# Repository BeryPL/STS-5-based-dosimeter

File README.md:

This is a terrible PCB design with LTSpice simulations for a STS-5 lamp based dosimeter circuit. This abomination is based on an old dosimeter design found on the internet, and was adopted to parts i had lying arround. Hence those weird resistor values and such. It does work tho. The goal is to create a fully working dosimeter circuit with a microcontroller for counting and sending information via BLE. 

Jest to okropny projekt PCB z symulacjami LTSpice dla obwodu dozymetru opartego na lampie STS-5. Ta abominacja jest oparta na starym projekcie dozymetru znalezionym w Internecie i została dostosowana do części, które miałem w pobliżu. Stąd te dziwne wartości rezystorów itp. Ale działa. Celem jest stworzenie w pełni działającego obwodu dozymetru z mikrokontrolerem do zliczania i wysyłania informacji przez BLE.

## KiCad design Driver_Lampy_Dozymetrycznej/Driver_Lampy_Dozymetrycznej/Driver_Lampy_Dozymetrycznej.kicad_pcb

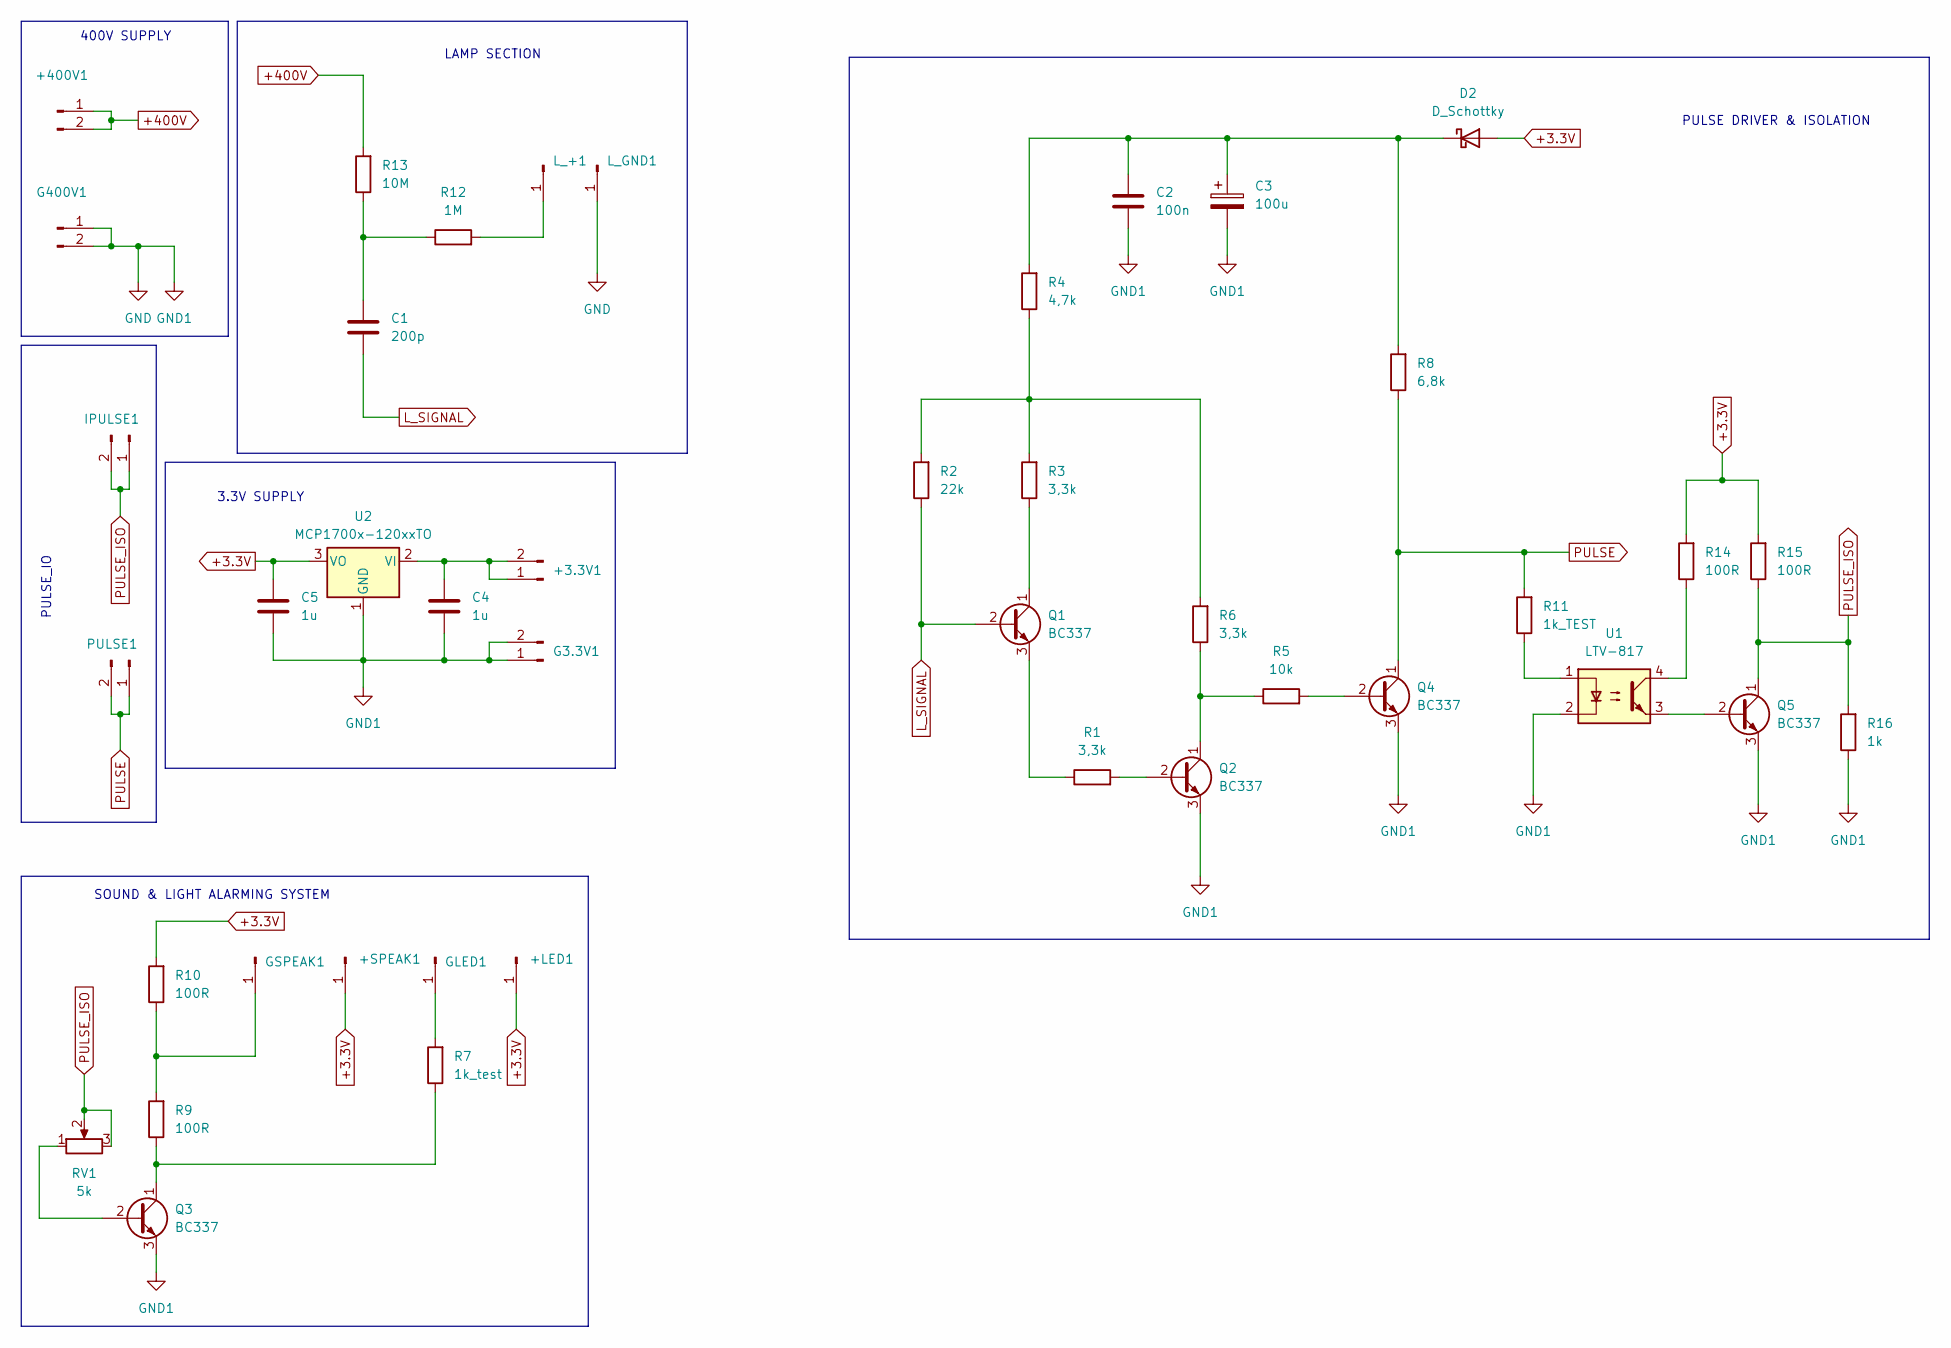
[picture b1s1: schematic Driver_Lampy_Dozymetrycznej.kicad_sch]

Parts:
+3.3V1, +400V1: Conn_01x02_Pin; PinHeader_1x02_P2.54mm_Horizontal
+LED1: Conn_01x01_Pin; PinHeader_1x01_P2.54mm_Horizontal
+SPEAK1: Conn_01x01_Pin; PinHeader_1x01_P2.54mm_Horizontal
C1: 200p; C_Disc_D6.0mm_W2.5mm_P5.00mm
C2: 100n; C_Disc_D6.0mm_W2.5mm_P5.00mm
C3: 100u; CP_Radial_D5.0mm_P2.00mm
C4, C5: 1u; C_Rect_L4.6mm_W2.0mm_P2.50mm_MKS02_FKP02
D2: D_Schottky; D_5KP_P10.16mm_Horizontal
G3.3V1, G400V1: Conn_01x02_Pin; PinHeader_1x02_P2.54mm_Horizontal
GLED1: Conn_01x01_Pin; PinHeader_1x01_P2.54mm_Horizontal
GSPEAK1: Conn_01x01_Pin; PinHeader_1x01_P2.54mm_Horizontal
IPULSE1: Conn_01x02_Pin; PinHeader_1x02_P2.54mm_Horizontal
L_+1: Conn_01x01_Pin; PinHeader_1x01_P2.54mm_Horizontal
L_GND1: Conn_01x01_Pin; PinHeader_1x01_P2.54mm_Horizontal
PULSE1: Conn_01x02_Pin; PinHeader_1x02_P2.54mm_Vertical
Q1, Q2, Q3, Q4, Q5: BC337; TO-92_Inline
R1, R3, R6: 3,3k; R_Axial_DIN0207_L6.3mm_D2.5mm_P10.16mm_Horizontal
R2: 22k; R_Axial_DIN0207_L6.3mm_D2.5mm_P10.16mm_Horizontal
R4: 4,7k; R_Axial_DIN0207_L6.3mm_D2.5mm_P10.16mm_Horizontal
R5: 10k; R_Axial_DIN0207_L6.3mm_D2.5mm_P10.16mm_Horizontal
R7: 1k_test; R_Axial_DIN0207_L6.3mm_D2.5mm_P10.16mm_Horizontal
R8: 6,8k; R_Axial_DIN0207_L6.3mm_D2.5mm_P10.16mm_Horizontal
R9, R10, R14, R15: 100R; R_Axial_DIN0207_L6.3mm_D2.5mm_P10.16mm_Horizontal
R11: 1k_TEST; R_Axial_DIN0207_L6.3mm_D2.5mm_P10.16mm_Horizontal
R12: 1M; R_Axial_DIN0207_L6.3mm_D2.5mm_P10.16mm_Horizontal
R13: 10M; R_Axial_DIN0207_L6.3mm_D2.5mm_P10.16mm_Horizontal
R16: 1k; R_Axial_DIN0207_L6.3mm_D2.5mm_P10.16mm_Horizontal
RV1: 5k; Potentiometer_ACP_CA9-V10_Vertical
U1: LTV-817; DIP-4_W7.62mm
U2: MCP1700x-120xxTO; TO-92_Inline

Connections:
+3.3V: +LED1.1, +SPEAK1.1, C5.1, D2.2 (A), R10.2, R14.2, R15.2, U2.3 (VO)
+400V: +400V1.1, +400V1.2, R13.2
GND: C2.2, C3.2, C4.2, C5.2, G3.3V1.1, G3.3V1.2, G400V1.1, G400V1.2, L_GND1.1, Q2.3 (E), Q3.3 (E), Q4.3 (E), Q5.3 (E), R16.1, U1.2, U2.1 (GND)
L_SIGNAL: C1.2, Q1.2 (B), R2.1
unnamed: +3.3V1.1, +3.3V1.2, C4.1, U2.2 (VI)
unnamed: C1.1, R12.1, R13.1
unnamed: C2.1, C3.1, D2.1 (K), R4.2, R8.2
unnamed: GLED1.1, R7.2
unnamed: GSPEAK1.1, R9.2, R10.1
unnamed: L_+1.1, R12.2
unnamed: Q1.1 (C), R3.1
unnamed: Q1.3 (E), R1.1
unnamed: Q2.2 (B), R1.2
unnamed: Q2.1 (C), R5.1, R6.1
unnamed: Q3.2 (B), RV1.1
unnamed: Q3.1 (C), R7.1, R9.1
unnamed: Q4.2 (B), R5.2
unnamed: Q5.2 (B), U1.3
unnamed: R2.2, R3.2, R4.1, R6.2
unnamed: R11.1, U1.1
unnamed: R14.1, U1.4
PULSE: PULSE1.1, PULSE1.2, Q4.1 (C), R8.1, R11.2
PULSE_ISO: IPULSE1.1, IPULSE1.2, Q5.1 (C), R15.1, R16.2, RV1.2, RV1.3

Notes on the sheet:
LAMP SECTION
3.3V SUPPLY
PULSE_IO
SOUND & LIGHT ALARMING SYSTEM
400V SUPPLY
PULSE DRIVER & ISOLATION

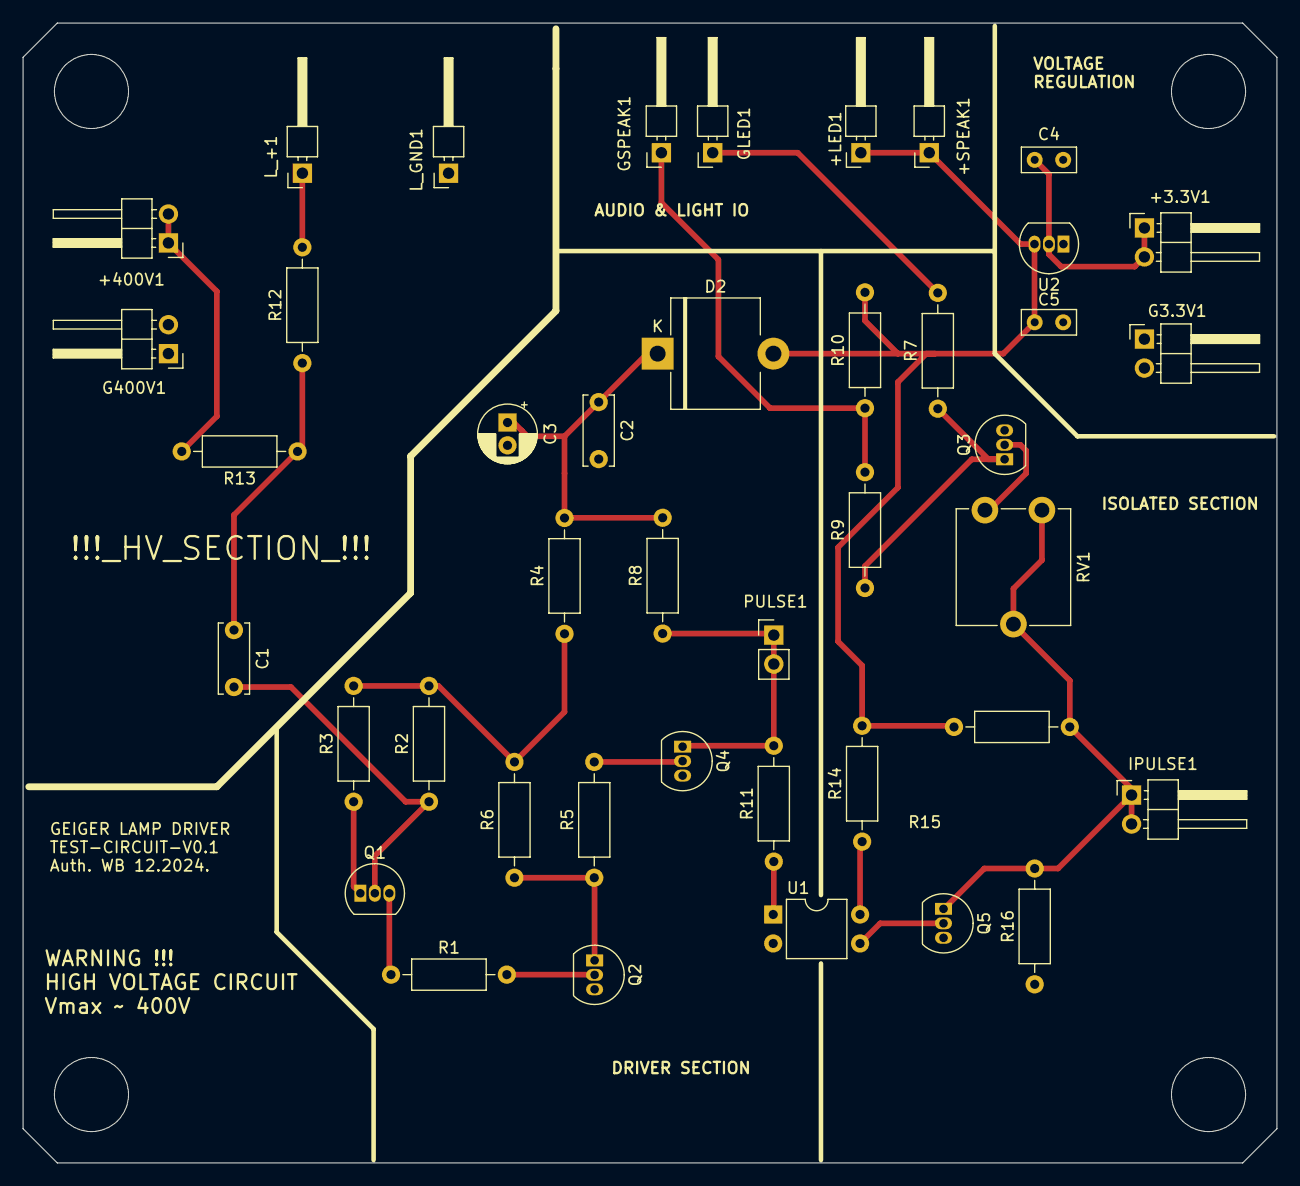
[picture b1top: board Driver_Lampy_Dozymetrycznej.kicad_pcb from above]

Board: 2 copper layers, 110.0 x 100.0 mm, 42 parts (0 on the bottom side), 23 nets.

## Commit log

2025-01-16 adding README
